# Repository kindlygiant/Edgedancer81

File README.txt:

Edgedancer81

Life before death.
Strength before weakness.
Journey before destination.

Beginner keyboard pcb 

Features:
81 key keyboard
Rotary encoder
No LED support
USB micro

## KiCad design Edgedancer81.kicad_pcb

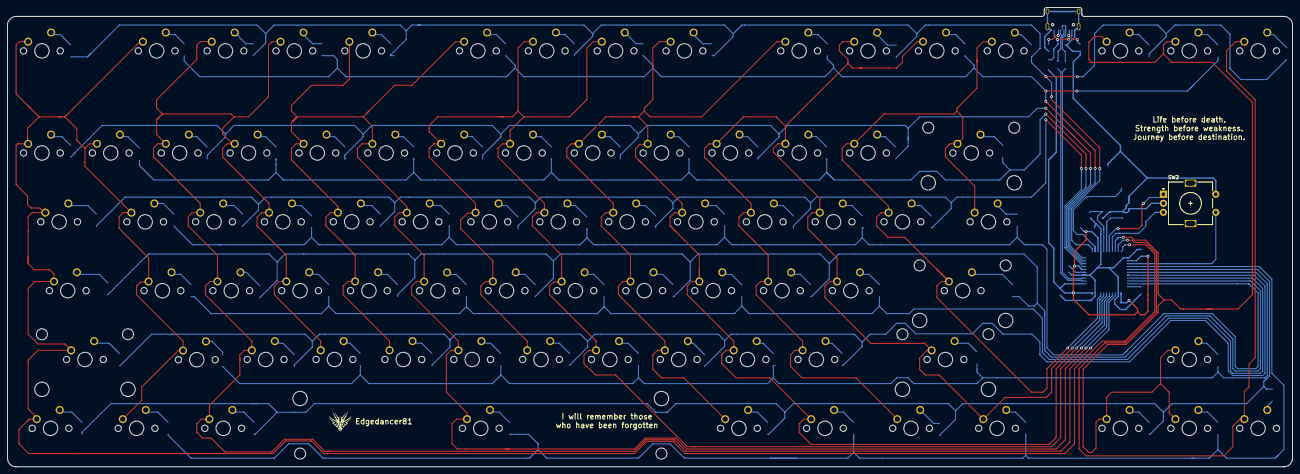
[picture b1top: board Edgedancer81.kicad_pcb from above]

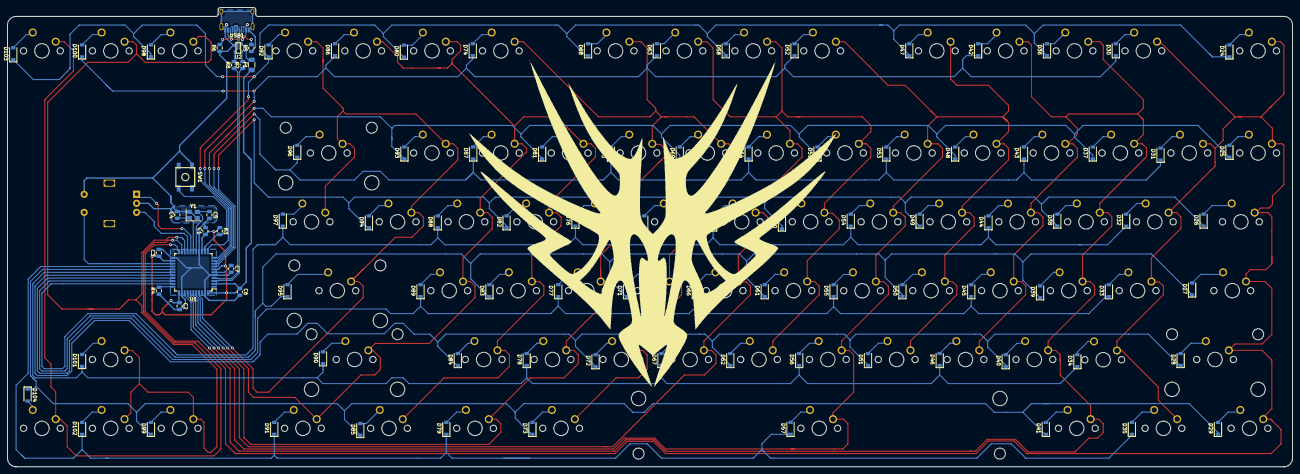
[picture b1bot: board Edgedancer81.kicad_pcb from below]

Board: 2 copper layers, 355.6 x 127.1 mm, 182 parts (100 on the bottom side), 119 nets.

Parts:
C1, C2, C3: 0.1uF; C_0805_2012Metric
C4, C5: 22pF; C_0805_2012Metric
C6: 10uF; C_0805_2012Metric
C7: 1uF; C_0805_2012Metric
D24, D25, D26, D27, D28, D29, D30, D31, D32, D33, D34, D35, D36, D37, D38, D39, D40, D41, D42, D43, D44, D45, D46, D47, D48, D49, D50, D51, D52, D53, D54, D55, D56, D57, D58, D59, D60, D61, D62, D63, D64, D65, D66, D67, D68, D69, D70, D71, D72, D73, D74, D75, D76, D77, D78, D79, D80, D81, D82, D83, D84, D85, D86, D87, D88, D89, D90, D91, D92, D93, D94, D95, D96, D97, D98, D99, D100, D101, D102, D103, D104: D_Small; D_SOD-123
F1: 500mA; Fuse_1206_3216Metric
MX0, MX1, MX2, MX3, MX4, MX5, MX6, MX7, MX8, MX9: MX-NoLED; MXOnly-1U-NoLED
MX-1: MX-NoLED; MXOnly-1U-NoLED
MX=1: MX-NoLED; MXOnly-1U-NoLED
MXBKSP1: MX-NoLED; MXOnly-2U-NoLED
MX_'1: MX-NoLED; MXOnly-1U-NoLED
MX_,1: MX-NoLED; MXOnly-1U-NoLED
MX_.1: MX-NoLED; MXOnly-1U-NoLED
MX_/1: MX-NoLED; MXOnly-1U-NoLED
MX_;1: MX-NoLED; MXOnly-1U-NoLED
MX_A1: MX-NoLED; MXOnly-1U-NoLED
MX_B1: MX-NoLED; MXOnly-1U-NoLED
MX_C1: MX-NoLED; MXOnly-1U-NoLED
MX_D1: MX-NoLED; MXOnly-1U-NoLED
MX_DOWN1: MX-NoLED; MXOnly-1U-NoLED
MX_E1: MX-NoLED; MXOnly-1U-NoLED
MX_ENTR1: MX-NoLED; MXOnly-2.25U-NoLED
MX_ESC1: MX-NoLED; MXOnly-1U-NoLED
MX_F1, MX_F2, MX_F3, MX_F4, MX_F5, MX_F6, MX_F7, MX_F8, MX_F9, MX_F10, MX_F11, MX_F12, MX_F13: MX-NoLED; MXOnly-1U-NoLED
MX_G1: MX-NoLED; MXOnly-1U-NoLED
MX_GUI1: MX-NoLED; MXOnly-1.25U-NoLED
MX_H1: MX-NoLED; MXOnly-1U-NoLED
MX_I1: MX-NoLED; MXOnly-1U-NoLED
MX_J1: MX-NoLED; MXOnly-1U-NoLED
MX_K1: MX-NoLED; MXOnly-1U-NoLED
MX_L1: MX-NoLED; MXOnly-1U-NoLED
MX_LALT1: MX-NoLED; MXOnly-1.25U-NoLED
MX_LCTRL1: MX-NoLED; MXOnly-1.25U-NoLED
MX_LEFT1: MX-NoLED; MXOnly-1U-NoLED
MX_LSHFT1: MX-NoLED; MXOnly-2.25U-NoLED
MX_M1: MX-NoLED; MXOnly-1U-NoLED
MX_N1: MX-NoLED; MXOnly-1U-NoLED
MX_NEXT1: MX-NoLED; MXOnly-1U-NoLED
MX_O1: MX-NoLED; MXOnly-1U-NoLED
MX_P1: MX-NoLED; MXOnly-1U-NoLED
MX_PLAY1: MX-NoLED; MXOnly-1U-NoLED
MX_PREV1: MX-NoLED; MXOnly-1U-NoLED
MX_Q1: MX-NoLED; MXOnly-1U-NoLED
MX_R1: MX-NoLED; MXOnly-1U-NoLED
MX_RALT1: MX-NoLED; MXOnly-1.25U-NoLED
MX_RCTRL1: MX-NoLED; MXOnly-1.25U-NoLED
MX_RGUI1: MX-NoLED; MXOnly-1.25U-NoLED
MX_RIGHT1: MX-NoLED; MXOnly-1U-NoLED
MX_RMENU1: MX-NoLED; MXOnly-1.25U-NoLED
MX_RSHFT1: MX-NoLED; MXOnly-2.75U-NoLED
MX_S1: MX-NoLED; MXOnly-1U-NoLED
MX_SPACE1: MX-NoLED; MXOnly-6.25U-ReversedStabilizers-NoLED
MX_SUPR1: MX-NoLED; MXOnly-1.75U-NoLED
MX_T1: MX-NoLED; MXOnly-1U-NoLED
MX_TAB1: MX-NoLED; MXOnly-1.5U-NoLED
MX_U1: MX-NoLED; MXOnly-1U-NoLED
MX_UP1: MX-NoLED; MXOnly-1U-NoLED
MX_V1: MX-NoLED; MXOnly-1U-NoLED
MX_W1: MX-NoLED; MXOnly-1U-NoLED
MX_X1: MX-NoLED; MXOnly-1U-NoLED
MX_Y1: MX-NoLED; MXOnly-1U-NoLED
MX_Z1: MX-NoLED; MXOnly-1U-NoLED
MX_[1: MX-NoLED; MXOnly-1U-NoLED
MX_\1: MX-NoLED; MXOnly-1.5U-NoLED
MX_]1: MX-NoLED; MXOnly-1U-NoLED
MX`1: MX-NoLED; MXOnly-1U-NoLED
R3, R4: 10k; R_0805_2012Metric
R5, R6: 5k1; R_0805_2012Metric
R7, R8: 22; R_0805_2012Metric
SW1: SW_Push; SKQG-1155865
SW2: Rotary_Encoder_Switch; RotaryEncoder_Alps_EC11E-Switch_Vertical_H20mm
U1: ATmega32U4-AU; TQFP-44_10x10mm_P0.8mm
U2: PRTR5V0U2X; SOT143B
USB1: HRO-TYPE-C-31-M-12; HRO-TYPE-C-31-M-12-Assembly
Y1: 16MHz; Crystal_SMD_3225-4Pin_3.2x2.5mm

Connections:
+5V: C1.1, C2.1, C3.1, C6.1, F1.1, R3.1, U1.2, U1.7, U1.14, U1.24, U1.34, U1.44
COL_0: MX1.1, MX_A1.1, MX_ESC1.1, MX_F1.1, MX_GUI1.1, MX_LCTRL1.1, MX_LSHFT1.1, MX_Q1.1, MX_SUPR1.1, MX_TAB1.1, MX_Z1.1, MX`1.1, U1.22
COL_1: MX2.1, MX3.1, MX_C1.1, MX_D1.1, MX_E1.1, MX_F2.1, MX_F3.1, MX_LALT1.1, MX_S1.1, MX_W1.1, MX_X1.1, U1.36
COL_2: MX4.1, MX5.1, MX_B1.1, MX_F4.1, MX_F5.1, MX_F13.1, MX_G1.1, MX_R1.1, MX_SPACE1.1, MX_T1.1, MX_V1.1, U1.37
COL_3: MX6.1, MX7.1, MX_F6.1, MX_F7.1, MX_H1.1, MX_J1.1, MX_M1.1, MX_N1.1, MX_U1.1, MX_Y1.1, U1.38
COL_4: MX8.1, MX9.1, MX_,1.1, MX_.1.1, MX_F8.1, MX_F9.1, MX_I1.1, MX_K1.1, MX_L1.1, MX_O1.1, MX_RALT1.1, MX_RGUI1.1, U1.39
COL_5: MX0.1, MX-1.1, MX_'1.1, MX_/1.1, MX_;1.1, MX_F10.1, MX_F11.1, MX_P1.1, MX_RCTRL1.1, MX_RMENU1.1, MX_RSHFT1.1, MX_[1.1, U1.40
COL_6: MX=1.1, MXBKSP1.1, MX_ENTR1.1, MX_F12.1, MX_\1.1, MX_]1.1, U1.41
COL_7: MX_DOWN1.1, MX_LEFT1.1, MX_PLAY1.1, MX_PREV1.1, MX_UP1.1, U1.20
COL_8: MX_NEXT1.1, MX_RIGHT1.1, U1.21
D+: R8.1, U1.4
D-: R7.1, U1.3
ENC_A: SW2.A, U1.18
ENC_B: SW2.B, U1.19
ENC_SW: SW2.S1, U1.25
GND: C1.2, C2.2, C3.2, C4.2, C5.2, C6.2, C7.2, R4.1, R5.1, R6.1, SW1.1, SW2.C, SW2.S2, U1.5, U1.15, U1.23, U1.35, U1.43, U2.1, USB1.1, USB1.12, USB1.13, Y1.2, Y1.4
unnamed: C4.1, U1.17, Y1.1
unnamed: C5.1, U1.16, Y1.3
unnamed: C7.1, U1.6
unnamed: D24.2, MX_ESC1.2
unnamed: D25.2, MX`1.2
unnamed: D26.2, MX_TAB1.2
unnamed: D27.2, MX_SUPR1.2
unnamed: D28.2, MX_LSHFT1.2
unnamed: D29.2, MX_LCTRL1.2
unnamed: D30.2, MX_F1.2
unnamed: D31.2, MX1.2
unnamed: D32.2, MX_Q1.2
unnamed: D33.2, MX_A1.2
unnamed: D34.2, MX_Z1.2
unnamed: D35.2, MX_GUI1.2
unnamed: D36.2, MX_F2.2
unnamed: D37.2, MX2.2
unnamed: D38.2, MX_W1.2
unnamed: D39.2, MX_S1.2
unnamed: D40.2, MX_X1.2
unnamed: D41.2, MX_LALT1.2
unnamed: D42.2, MX_F3.2
unnamed: D43.2, MX3.2
unnamed: D44.2, MX_E1.2
unnamed: D45.2, MX_D1.2
unnamed: D46.2, MX_C1.2
unnamed: D47.2, MX_F4.2
unnamed: D48.2, MX4.2
unnamed: D49.2, MX_R1.2
unnamed: D50.2, MX_F13.2
unnamed: D51.2, MX_V1.2
unnamed: D52.2, MX_F5.2
unnamed: D53.2, MX5.2
unnamed: D54.2, MX_T1.2
unnamed: D55.2, MX_G1.2
unnamed: D56.2, MX_B1.2
unnamed: D57.2, MX_SPACE1.2
unnamed: D58.2, MX_F6.2
unnamed: D59.2, MX6.2
unnamed: D60.2, MX_Y1.2
unnamed: D61.2, MX_H1.2
unnamed: D62.2, MX_N1.2
unnamed: D63.2, MX_F7.2
unnamed: D64.2, MX7.2
unnamed: D65.2, MX_U1.2
unnamed: D66.2, MX_J1.2
unnamed: D67.2, MX_M1.2
unnamed: D68.2, MX_F8.2
unnamed: D69.2, MX8.2
unnamed: D70.2, MX_I1.2
unnamed: D71.2, MX_K1.2
unnamed: D72.2, MX_,1.2
unnamed: D73.2, MX_RALT1.2
unnamed: D74.2, MX_F9.2
unnamed: D75.2, MX9.2
unnamed: D76.2, MX_O1.2
unnamed: D77.2, MX_L1.2
unnamed: D78.2, MX_.1.2
unnamed: D79.2, MX_RGUI1.2
unnamed: D80.2, MX_F10.2
unnamed: D81.2, MX0.2
unnamed: D82.2, MX_P1.2
unnamed: D83.2, MX_;1.2
unnamed: D84.2, MX_/1.2
unnamed: D85.2, MX_RMENU1.2
unnamed: D86.2, MX_F11.2
unnamed: D87.2, MX-1.2
unnamed: D88.2, MX_[1.2
unnamed: D89.2, MX_'1.2
unnamed: D90.2, MX_RSHFT1.2
unnamed: D91.2, MX_RCTRL1.2
unnamed: D92.2, MX_F12.2
unnamed: D93.2, MX=1.2
unnamed: D94.2, MX_]1.2
unnamed: D95.2, MX_ENTR1.2
unnamed: D96.2, MXBKSP1.2
unnamed: D97.2, MX_\1.2
unnamed: D98.2, MX_PREV1.2
unnamed: D99.2, MX_LEFT1.2
unnamed: D100.2, MX_PLAY1.2
unnamed: D101.2, MX_UP1.2
unnamed: D102.2, MX_DOWN1.2
unnamed: D103.2, MX_NEXT1.2
unnamed: D104.2, MX_RIGHT1.2
unnamed: R3.2, SW1.2, U1.13
unnamed: R4.2, U1.33
unnamed: R5.2, USB1.4
unnamed: R6.2, USB1.10
unnamed: R7.2, U2.3, USB1.5, USB1.7
unnamed: R8.2, U2.2, USB1.6, USB1.8
ROW_0: D24.1, D36.1, D47.1, D58.1, D68.1, D80.1, D92.1, D98.1, D103.1, U1.12
ROW_1: D30.1, D42.1, D52.1, D63.1, D74.1, D86.1, D100.1, U1.11
ROW_2: D25.1, D37.1, D48.1, D59.1, D69.1, D81.1, D93.1, U1.10
ROW_3: D31.1, D43.1, D53.1, D64.1, D75.1, D87.1, D96.1, U1.9
ROW_4: D26.1, D38.1, D49.1, D60.1, D70.1, D82.1, D94.1, U1.8
ROW_5: D32.1, D44.1, D54.1, D65.1, D76.1, D88.1, D97.1, U1.32
ROW_6: D27.1, D39.1, D50.1, D61.1, D71.1, D83.1, D95.1, U1.31
ROW_7: D33.1, D45.1, D55.1, D66.1, D77.1, D89.1, U1.30
ROW_8: D28.1, D40.1, D51.1, D62.1, D72.1, D84.1, U1.29
ROW_9: D34.1, D46.1, D56.1, D67.1, D78.1, D90.1, D101.1, U1.28
ROW_10: D29.1, D41.1, D73.1, D85.1, D99.1, D104.1, U1.27
ROW_11: D35.1, D57.1, D79.1, D91.1, D102.1, U1.26
VCC: F1.2, U2.4, USB1.2, USB1.11

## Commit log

2020-07-13 Added Submodules from ai03
2020-07-13 Add footprint libraries
2020-07-13 MCU Schematic
2020-07-13 more wires
2020-07-21 traces
2020-07-21 silkscreen and bugfixes
2020-07-21 restructured keys
2020-07-22 Created Gerbers
2020-07-22 fixing acute angles in traces
2020-07-22 final traces
2020-07-22 added render and readme
2020-07-22 Updated Gerber files
2020-07-22 added plate layout details
2020-07-31 step file created
2020-07-31 the plate, you know, the one to support the keys.
    needs stuff added for support and stabilizer holes
2020-07-31 Updated for type-c
    Still needs to update the pcb
2020-08-05 Finished traces
2020-08-05 cleaned up data traces
